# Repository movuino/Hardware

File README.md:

# Hardware
Hardware files of the Movuino boards.

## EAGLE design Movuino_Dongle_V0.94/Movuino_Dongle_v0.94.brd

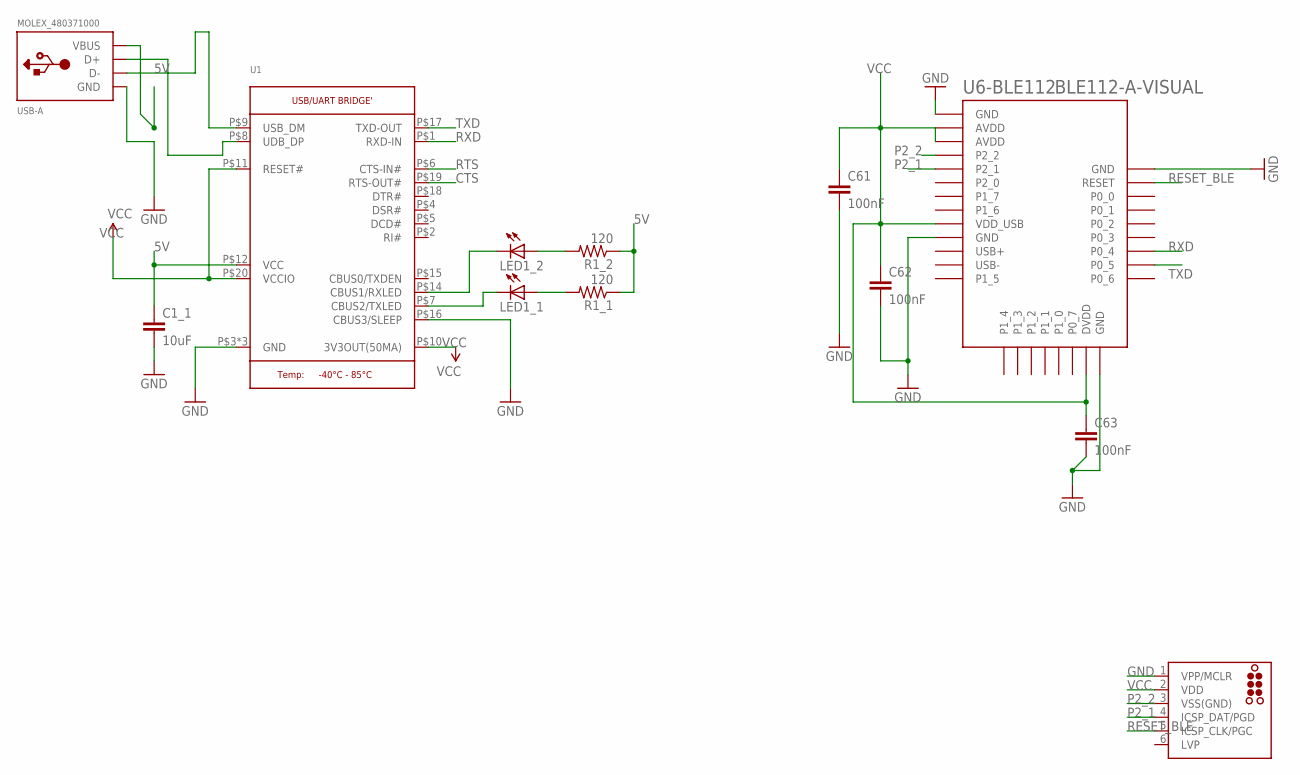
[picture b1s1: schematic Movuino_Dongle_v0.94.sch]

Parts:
C1_1: 10uF; 0402-CAP
C61, C62, C63: 100nF; 0402-CAP
J1: TC2030-MCP-NL
LED1_1, LED1_2: LED0603; LED-0603
MOLEX_480371000: USB-A; MOLEX_480371000
R1_1, R1_2: 120; 0402-RES
U1: MICROBUILDER_FT231X; MICROBUILDER_QFN20_4MM
U6-BLE112: BLE112-A-VISUAL; BLE112-A

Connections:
5V: C1_1.1, MOLEX_480371000.1 (VBUS), R1_1.1, R1_2.1, U1.P$12 (VCC)
CTS: U1.P$19 (RTS-OUT#)
GND: C1_1.2, C61.2, C62.2, C63.2, J1.1 (VPP/MCLR), MOLEX_480371000.4 (GND), U1.P$3 (GND), U1.P$13 (GND), U1.P$16 (CBUS3/SLEEP), U1.P$21 (GND), U6-BLE112.GND1 (GND), U6-BLE112.GND2 (GND), U6-BLE112.GND3 (GND), U6-BLE112.GND4 (GND)
unnamed: MOLEX_480371000.3 (D+), U1.P$8 (UDB_DP)
unnamed: MOLEX_480371000.2 (D-), U1.P$9 (USB_DM)
unnamed: LED1_2.C, U1.P$14 (CBUS1/RXLED)
unnamed: LED1_1.C, U1.P$7 (CBUS2/TXLED)
unnamed: LED1_2.A, R1_2.2
unnamed: LED1_1.A, R1_1.2
P2_1: J1.4 (ICSP_DAT/PGD), U6-BLE112.P2_1
P2_2: J1.3 (VSS(GND)), U6-BLE112.P2_2
RESET_BLE: J1.5 (ICSP_CLK/PGC), U6-BLE112.RESET
RTS: U1.P$6 (CTS-IN#)
RXD: U1.P$1 (RXD-IN), U6-BLE112.P0_4
TXD: U1.P$17 (TXD-OUT), U6-BLE112.P0_5
VCC: C61.1, C62.1, C63.1, J1.2 (VDD), U1.P$10 (3V3OUT(50MA)), U1.P$11 (RESET#), U1.P$20 (VCCIO), U6-BLE112.AVDD1 (AVDD), U6-BLE112.AVDD2 (AVDD), U6-BLE112.DVDD, U6-BLE112.VDD_USB

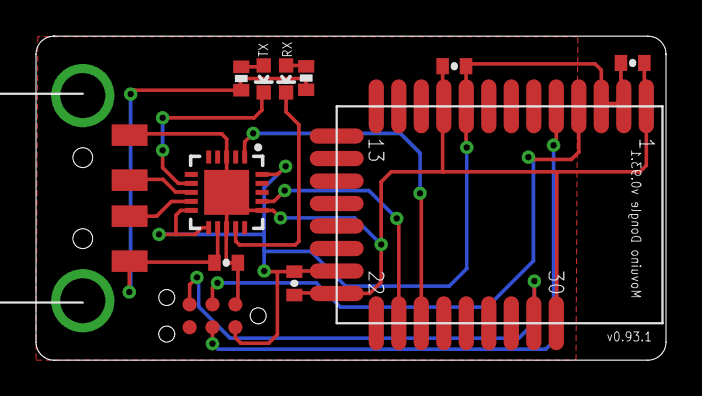
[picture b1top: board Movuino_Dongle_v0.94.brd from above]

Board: 4 copper layers, 35.0 x 18.0 mm, 12 parts (0 on the bottom side), 14 nets.

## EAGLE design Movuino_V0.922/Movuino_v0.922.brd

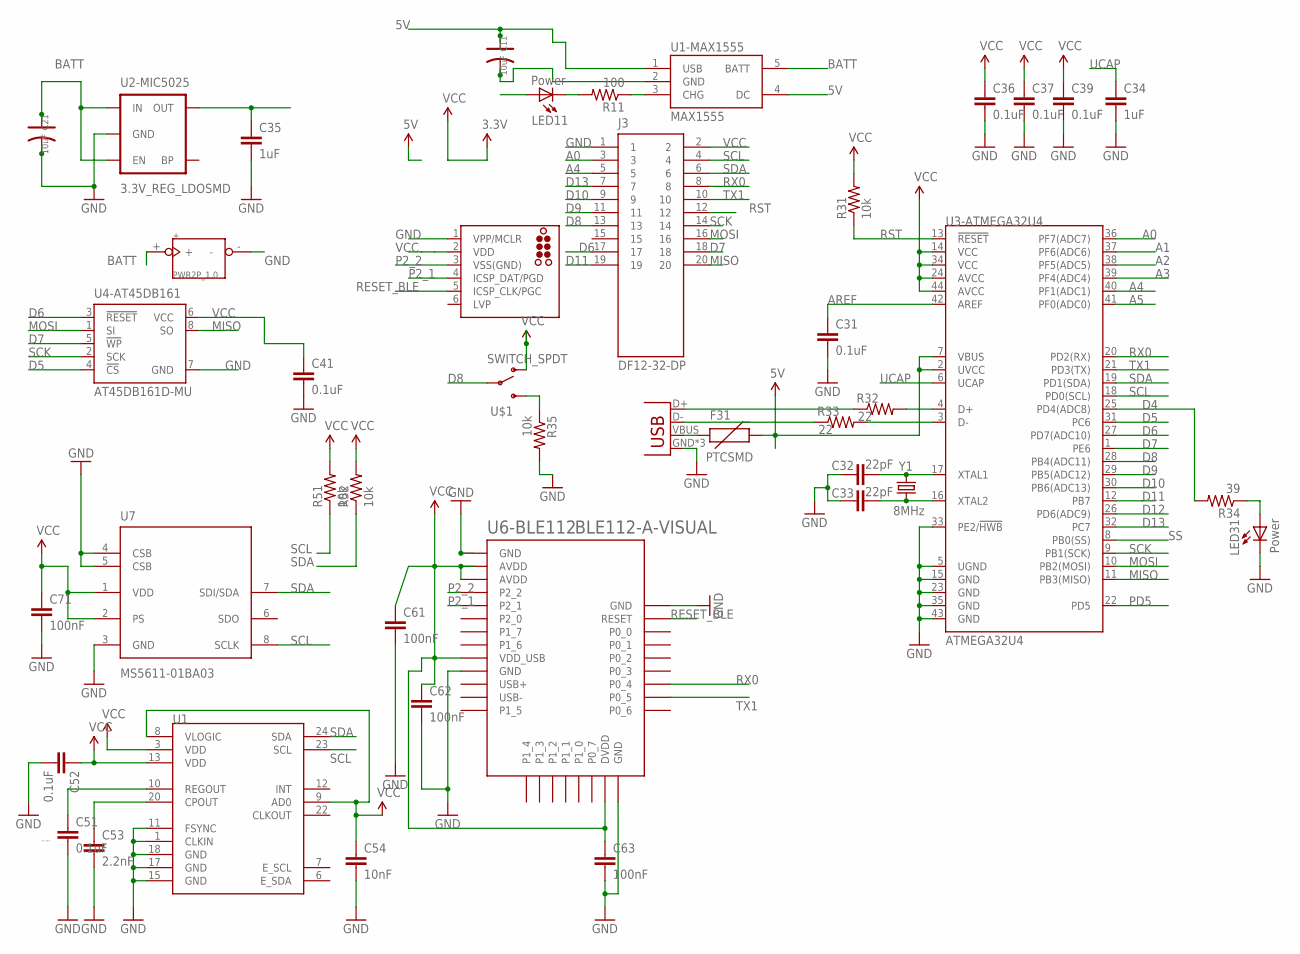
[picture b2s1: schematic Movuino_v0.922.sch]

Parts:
+: PWR2P_1.0
C11, C21: 10uF; AVX-A
C31, C36, C37, C39, C41, C51, C52: 0.1uF; 0402-CAP
C32, C33: 22pF; 0402-CAP
C34, C35: 1uF; 0402-CAP
C53: 2.2nF; 0402-CAP
C54: 10nF; 0402-CAP
C61, C62, C63, C71: 100nF; 0402-CAP
F31: PTCSMD; PTC-1206
J1: TC2030-MCP-NL
J3: DF12-32-DP; DF12-20-DP
LED11, LED31: Power; LED-0603
R11: 100; 0402-RES
R31, R35, R51, R52: 10k; 0402-RES
R32, R33: 22; 0402-RES
R34: 39; 0402-RES
U1: MPU-9150QFN-24-NP; QFN-24-NP
U1-MAX1555: MAX1555; SOT23-5
U2-MIC5025: 3.3V_REG_LDOSMD; SOT23-5
U3-ATMEGA32U4: ATMEGA32U4; QFN-44-NOPAD
U4-AT45DB161: AT45DB161D-MU; VDFN-8
U6-BLE112: BLE112-A-VISUAL; BLE112-A
U7: MS5611-01BA03; SON125P300X500X100-8N
U$1: SWITCH_SPDT; KPS-1290
X1: USB-MICROB
Y1: 8MHz; CRYSTAL-SMD-5X3

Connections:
5V: C11.+ (1), F31.2, U1-MAX1555.1 (USB), U1-MAX1555.4 (DC), U3-ATMEGA32U4.2 (UVCC), U3-ATMEGA32U4.7 (VBUS)
A0: J3.3, U3-ATMEGA32U4.36 (PF7(ADC7))
A1: U3-ATMEGA32U4.37 (PF6(ADC6))
A2: U3-ATMEGA32U4.38 (PF5(ADC5))
A3: U3-ATMEGA32U4.39 (PF4(ADC4))
A4: J3.5, U3-ATMEGA32U4.40 (PF1(ADC1))
A5: U3-ATMEGA32U4.41 (PF0(ADC0))
AREF: C31.1, U3-ATMEGA32U4.42 (AREF)
BATT: +.+, C21.+ (1), LED11.A, U1-MAX1555.5 (BATT), U2-MIC5025.1 (IN), U2-MIC5025.3 (EN)
D4: R34.2, U3-ATMEGA32U4.25 (PD4(ADC8))
D5: U3-ATMEGA32U4.31 (PC6), U4-AT45DB161.4 (!CS)
D6: J3.17, U3-ATMEGA32U4.27 (PD7(ADC10)), U4-AT45DB161.3 (!RESET)
D7: J3.18, U3-ATMEGA32U4.1 (PE6), U4-AT45DB161.5 (!WP)
D8: J3.13, U3-ATMEGA32U4.28 (PB4(ADC11)), U$1.P
D9: J3.11, U3-ATMEGA32U4.29 (PB5(ADC12))
D10: J3.9, U3-ATMEGA32U4.30 (PB6(ADC13))
D11: J3.19, U3-ATMEGA32U4.12 (PB7)
D12: U3-ATMEGA32U4.26 (PD6(ADC9))
D13: J3.7, U3-ATMEGA32U4.32 (PC7)
D+: R32.1, X1.D+
D-: R33.1, X1.D-
GND: +.-, C11.- (2), C21.- (2), C31.2, C32.1, C33.1, C34.2, C35.2, C36.2, C37.2, C39.2, C41.2, C51.2, C52.2, C53.2, C54.2, C61.2, C62.2, C63.2, C71.2, J1.1 (VPP/MCLR), J3.1, LED31.C, R35.2, U1.1 (CLKIN), U1.11 (FSYNC), U1.15 (GND), U1.17 (GND), U1.18 (GND), U1-MAX1555.2 (GND), U2-MIC5025.2 (GND), U3-ATMEGA32U4.5 (UGND), U3-ATMEGA32U4.15 (GND), U3-ATMEGA32U4.23 (GND), U3-ATMEGA32U4.33 (PE2/!HWB), U3-ATMEGA32U4.35 (GND), U3-ATMEGA32U4.43 (GND), U4-AT45DB161.7 (GND), U6-BLE112.GND1 (GND), U6-BLE112.GND2 (GND), U6-BLE112.GND3 (GND), U6-BLE112.GND4 (GND), U7.3 (GND), U7.4 (CSB), U7.5 (CSB), X1.GND, X1.MT1 (GND), X1.MT2 (GND)
MISO: J3.20, U3-ATMEGA32U4.11 (PB3(MISO)), U4-AT45DB161.8 (SO)
MOSI: J3.16, U3-ATMEGA32U4.10 (PB2(MOSI)), U4-AT45DB161.1 (SI)
unnamed: C32.2, U3-ATMEGA32U4.17 (XTAL1), Y1.3 (2)
unnamed: C33.2, U3-ATMEGA32U4.16 (XTAL2), Y1.1
unnamed: F31.1, X1.VBUS
unnamed: R32.2, U3-ATMEGA32U4.4 (D+)
unnamed: R11.1, U1-MAX1555.3 (CHG)
unnamed: R33.2, U3-ATMEGA32U4.3 (D-)
unnamed: LED11.C, R11.2
unnamed: C51.1, U1.10 (REGOUT)
unnamed: C53.1, U1.20 (CPOUT)
unnamed: LED31.A, R34.1
unnamed: R35.1, U$1.S
P2_1: J1.4 (ICSP_DAT/PGD), U6-BLE112.P2_1
P2_2: J1.3 (VSS(GND)), U6-BLE112.P2_2
PD5: U3-ATMEGA32U4.22 (PD5)
RESET_BLE: J1.5 (ICSP_CLK/PGC), U6-BLE112.RESET
RST: J3.12, R31.1, U3-ATMEGA32U4.13 (!RESET)
RX0: J3.8, U3-ATMEGA32U4.20 (PD2(RX)), U6-BLE112.P0_4
SCK: J3.14, U3-ATMEGA32U4.9 (PB1(SCK)), U4-AT45DB161.2 (SCK)
SCL: J3.4, R51.1, U1.23 (SCL), U3-ATMEGA32U4.18 (PD0(SCL)), U7.8 (SCLK)
SDA: J3.6, R52.1, U1.24 (SDA), U3-ATMEGA32U4.19 (PD1(SDA)), U7.7 (SDI/SDA)
SS: U3-ATMEGA32U4.8 (PB0(SS))
TX1: J3.10, U3-ATMEGA32U4.21 (PD3(TX)), U6-BLE112.P0_5
UCAP: C34.1, U3-ATMEGA32U4.6 (UCAP)
VCC: C35.1, C36.1, C37.1, C39.1, C41.1, C52.1, C54.1, C61.1, C62.1, C63.1, C71.1, J1.2 (VDD), J3.2, R31.2, R51.2, R52.2, U1.3 (VDD), U1.8 (VLOGIC), U1.9 (AD0), U1.13 (VDD), U2-MIC5025.5 (OUT), U3-ATMEGA32U4.14 (VCC), U3-ATMEGA32U4.24 (AVCC), U3-ATMEGA32U4.34 (VCC), U3-ATMEGA32U4.44 (AVCC), U4-AT45DB161.6 (VCC), U6-BLE112.AVDD1 (AVDD), U6-BLE112.AVDD2 (AVDD), U6-BLE112.DVDD, U6-BLE112.VDD_USB, U7.1 (VDD), U7.2 (PS), U$1.O

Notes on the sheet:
DC_V0.9

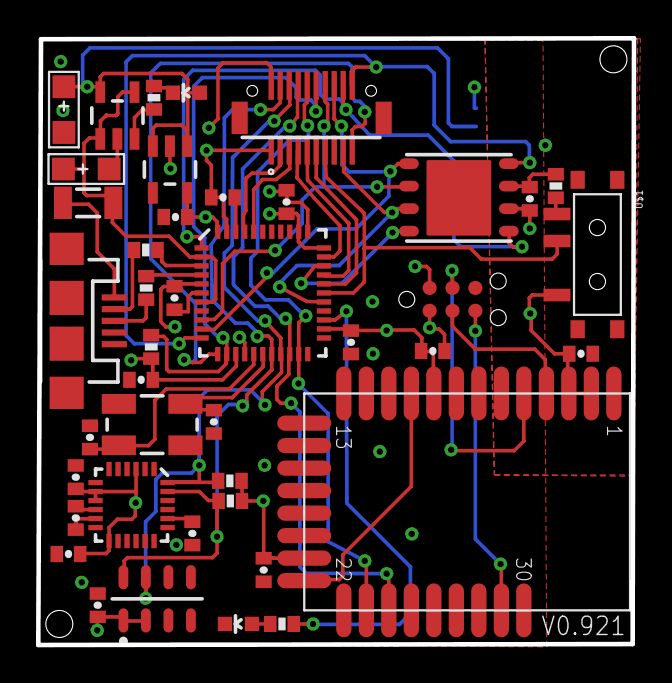
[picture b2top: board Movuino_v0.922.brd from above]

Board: 4 copper layers, 33.1 x 33.7 mm, 43 parts (1 on the bottom side), 41 nets.

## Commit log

2016-07-11 Added Movuino board V0.922
    ATmega32U4
    BLE112
    MPU9150
    MS5611
    AT45db161
2016-07-11 Added Movuino Dongle V0.94 fikes

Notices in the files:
parts and their libraries:
SparkFun-LED: Licensing: CC v3.0 Share-Alike You are welcome to use this library for commercial purposes.
tag-connect: ©2009 ROFA.cz - modified and updated by Robert Darlington ‹rdarlington@gmail.com›
